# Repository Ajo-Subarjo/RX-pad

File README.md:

# RX-pad

A custom 3×3 macropad built with a seed xiao rp2040 and KMK firmware.

The macropad includes media controls, and soon will adding blender shortcut layer, a rotary encoder for volume control, an OLED display, and RGB LEDs.

## Features

* 3×3 key matrix  (if the switch in encoder count)
* Media controls
  * Previous track
  * Next track
  * Play/Pause
  * Stop
  * Mute
* Function layer
  * F1–F8
    
* Rotary encoder
  * Clockwise → Volume Up
  * Counter-clockwise → Volume Down
* 128×32 I2C OLED
* 12 NeoPixel LEDs
* Layer switching with a dedicated key
* KMK firmware

### Schematic

### Pcb

### Case

### Overall look

### Final look

## BOM:
* Seeed XIAO RP2040
* 9x through-hole 1N4148 Diodes
* 8x MX-Style switches
* 1x EC11E Rotary encoders (with switch!)
* 1x 0.91 inch OLED display
* 8x keycaps
* 12x SK6812 MINI-E LEDs
* 4x M3x16mm screws
* 4x M3x5mx4mm heatset inserts
* 4 3D printed parts

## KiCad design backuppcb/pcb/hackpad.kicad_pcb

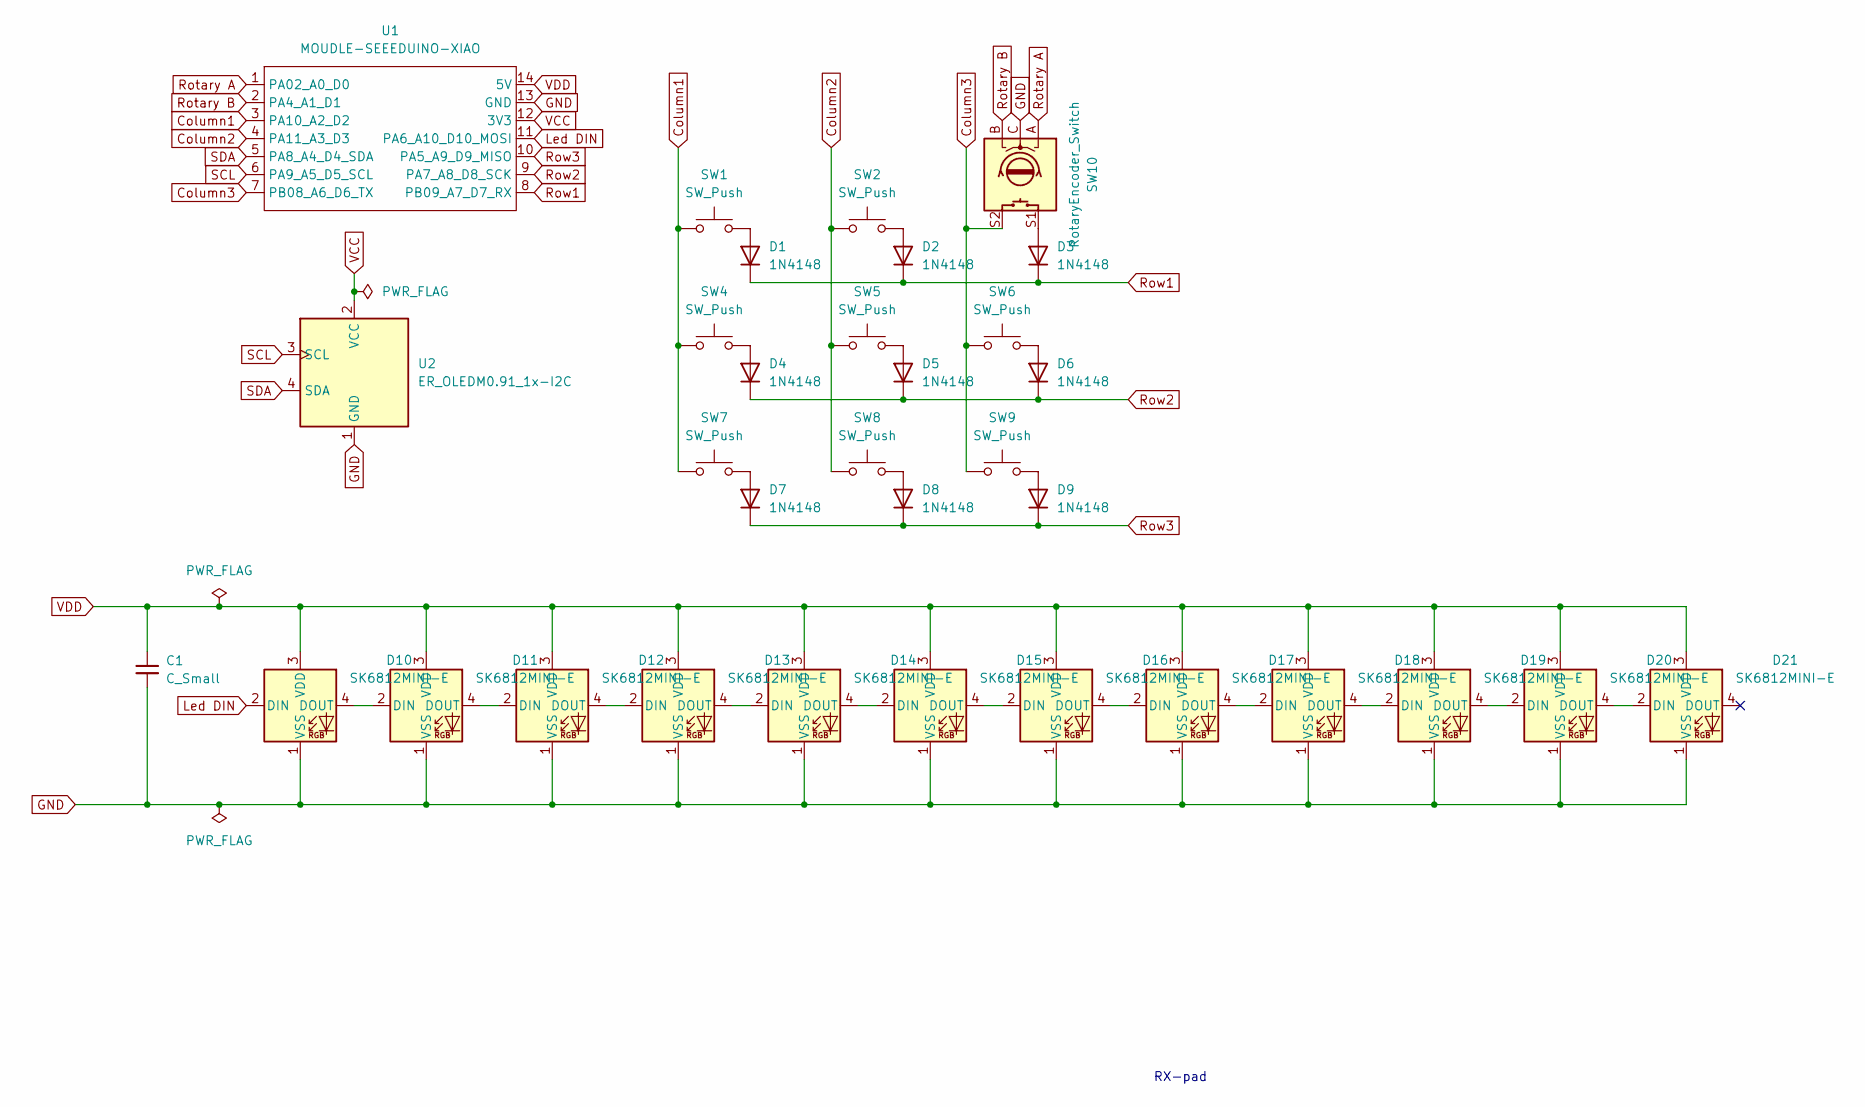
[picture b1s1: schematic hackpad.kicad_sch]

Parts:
C1: C_Small; CP_Radial_D5.0mm_P2.00mm
D1, D2, D3, D4, D5, D6, D7, D8, D9: 1N4148; D_DO-35_SOD27_P7.62mm_Horizontal
D10, D11, D12, D13, D14, D15, D16, D17, D18, D19, D20, D21: SK6812MINI-E; LED_SK6812MINI-E_3.2x2.8mm_P1.5mm_ReverseMount
SW1, SW2, SW4, SW5, SW6, SW7, SW8, SW9: SW_Push; SW_Cherry_MX_1.00u_PCB
SW10: RotaryEncoder_Switch; RotaryEncoder_Alps_EC11E-Switch_Vertical_H20mm
U1: MOUDLE-SEEEDUINO-XIAO; XIAO-Generic-Hybrid-14P-2.54-21X17.8MM
U2: ER_OLEDM0.91_1x-I2C

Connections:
Column1: SW1.1, SW4.1, SW7.1, U1.3 (PA10_A2_D2)
Column2: SW2.1, SW5.1, SW8.1, U1.4 (PA11_A3_D3)
Column3: SW6.1, SW9.1, SW10.S2, U1.7 (PB08_A6_D6_TX)
GND: C1.2, D10.1 (VSS), D11.1 (VSS), D12.1 (VSS), D13.1 (VSS), D14.1 (VSS), D15.1 (VSS), D16.1 (VSS), D17.1 (VSS), D18.1 (VSS), D19.1 (VSS), D20.1 (VSS), D21.1 (VSS), SW10.C, U1.13 (GND), U2.1 (GND)
Led DIN: D10.2 (DIN), U1.11 (PA6_A10_D10_MOSI)
unnamed: D1.2 (A), SW1.2
unnamed: D2.2 (A), SW2.2
unnamed: D3.2 (A), SW10.S1
unnamed: D4.2 (A), SW4.2
unnamed: D5.2 (A), SW5.2
unnamed: D6.2 (A), SW6.2
unnamed: D7.2 (A), SW7.2
unnamed: D8.2 (A), SW8.2
unnamed: D9.2 (A), SW9.2
unnamed: D10.4 (DOUT), D11.2 (DIN)
unnamed: D11.4 (DOUT), D12.2 (DIN)
unnamed: D12.4 (DOUT), D13.2 (DIN)
unnamed: D13.4 (DOUT), D14.2 (DIN)
unnamed: D14.4 (DOUT), D15.2 (DIN)
unnamed: D15.4 (DOUT), D16.2 (DIN)
unnamed: D16.4 (DOUT), D17.2 (DIN)
unnamed: D17.4 (DOUT), D18.2 (DIN)
unnamed: D18.4 (DOUT), D19.2 (DIN)
unnamed: D19.4 (DOUT), D20.2 (DIN)
unnamed: D20.4 (DOUT), D21.2 (DIN)
Rotary A: SW10.A, U1.1 (PA02_A0_D0)
Rotary B: SW10.B, U1.2 (PA4_A1_D1)
Row1: D1.1 (K), D2.1 (K), D3.1 (K), U1.8 (PB09_A7_D7_RX)
Row2: D4.1 (K), D5.1 (K), D6.1 (K), U1.9 (PA7_A8_D8_SCK)
Row3: D7.1 (K), D8.1 (K), D9.1 (K), U1.10 (PA5_A9_D9_MISO)
SCL: U1.6 (PA9_A5_D5_SCL), U2.3 (SCL)
SDA: U1.5 (PA8_A4_D4_SDA), U2.4 (SDA)
VCC: U1.12 (3V3), U2.2 (VCC)
VDD: C1.1, D10.3 (VDD), D11.3 (VDD), D12.3 (VDD), D13.3 (VDD), D14.3 (VDD), D15.3 (VDD), D16.3 (VDD), D17.3 (VDD), D18.3 (VDD), D19.3 (VDD), D20.3 (VDD), D21.3 (VDD), U1.14 (5V)

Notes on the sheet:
RX-pad

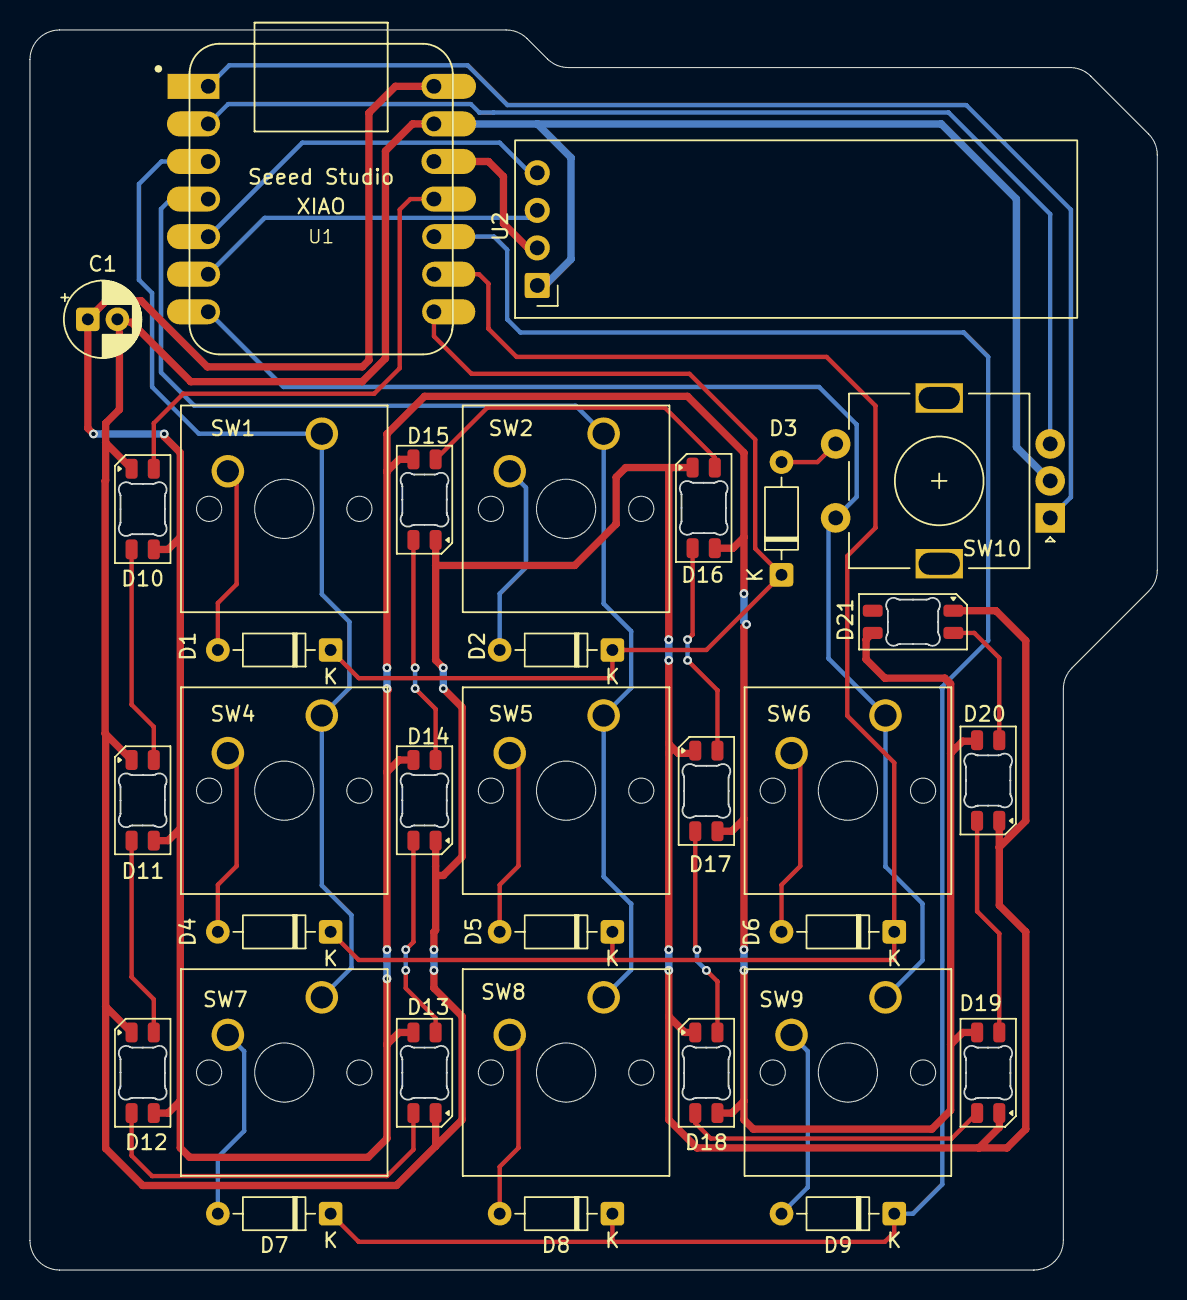
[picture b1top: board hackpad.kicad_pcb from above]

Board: 2 copper layers, 76.2 x 83.8 mm, 33 parts (0 on the bottom side), 34 nets.

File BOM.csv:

Reference,Qty,Value,DNP,Exclude from BOM,Exclude from Board,Exclude from Simulation,Exclude from Position Files,Footprint,Datasheet
"D1,D2,D3,D4,D5,D6,D7,D8,D9",9,1N4148,,,,,${EXCLUDE_FROM_POS_FILES},Diode_THT:D_DO-35_SOD27_P7.62mm_Horizontal,https://assets.nexperia.com/documents/data-sheet/1N4148_1N4448.pdf
"D10,D11,D12,D13,D14,D15,D16,D17,D18,D19,D20,D21",12,SK6812MINI-E,,,,,${EXCLUDE_FROM_POS_FILES},LED_SMD:LED_SK6812MINI-E_3.2x2.8mm_P1.5mm_ReverseMount,https://www.lcsc.com/datasheet/C5149201.pdf
"SW1,SW2,SW4,SW5,SW6,SW7,SW8,SW9",8,SW_Push,,,,,${EXCLUDE_FROM_POS_FILES},Button_Switch_Keyboard:SW_Cherry_MX_1.00u_PCB,
SW10,1,RotaryEncoder_Switch,,,,,${EXCLUDE_FROM_POS_FILES},Rotary_Encoder:RotaryEncoder_Alps_EC11E-Switch_Vertical_H20mm,
U1,1,MOUDLE-SEEEDUINO-XIAO,,,,,${EXCLUDE_FROM_POS_FILES},footprints:XIAO-Generic-Hybrid-14P-2.54-21X17.8MM,
U2,1,ER_OLEDM0.91_1x-I2C,,,,,${EXCLUDE_FROM_POS_FILES},Display:ER_OLEDM0.91_1x-I2C,https://www.buydisplay.com/download/manual/ER-OLEDM0.91-1_Da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
,,,,,,,,,
,,,,,,,,,
,4,3D print,,,,,,,
,1,PCB,,,,,,,
,8,Keycaps,,,,,,,
